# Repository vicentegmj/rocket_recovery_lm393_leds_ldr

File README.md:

# rocket_recovery_lm393_leds_uv

Sistema eletrônico cuja funcionalidade prevista é liberar um paraquedas logo após atingir o apogeu da trajetória do lançamento. O funcionamento do cirtuto é basedo no monitoramento de tensões elétricas em duas portas analógicas do CI LM393, as tensões são geradas por 2 LEDs UV. LED UV tem a paricularidade de criar uma tensão V nos seus terminais quando exposta á luz ultravioleta, no caso do foguete, a luz ultravioleta do Sol. Quando há inversão da tensão nos terminais o LM393 atravéz do seu pino de saída faz a saturação do TIP122 que passa a conduzir corrente elétrica direta da bateria de 9V fazendo a ignição da carga.

Esquema elétrico 26-06-2025

Circuito placa 11/07/2025

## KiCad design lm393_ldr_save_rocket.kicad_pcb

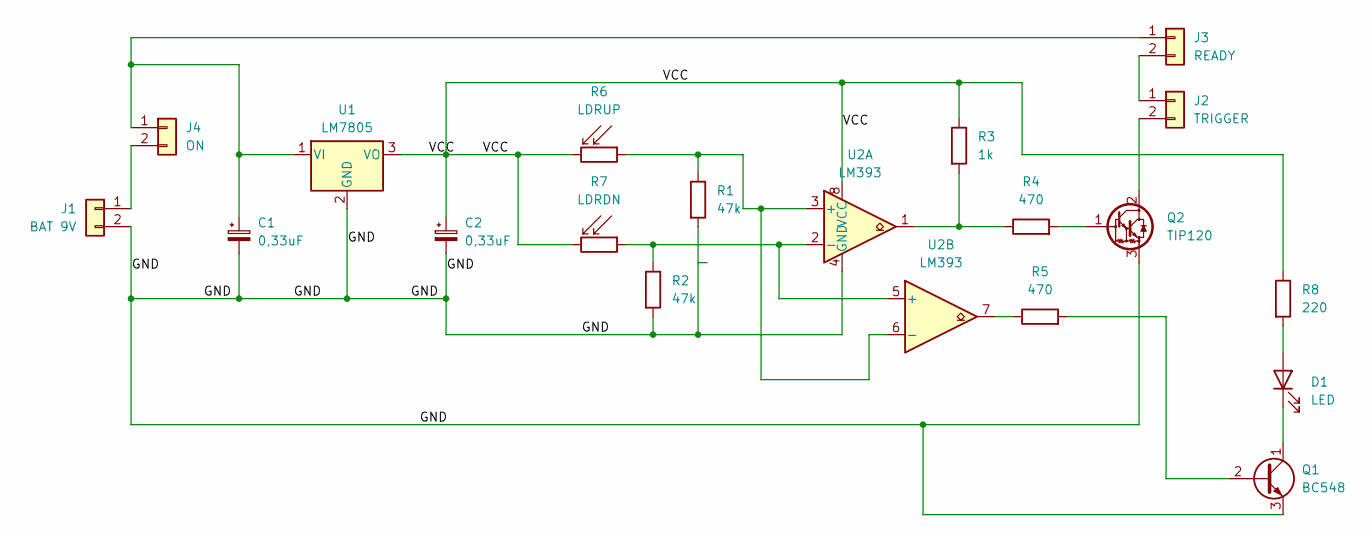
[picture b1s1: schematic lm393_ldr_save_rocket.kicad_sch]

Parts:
C1, C2: 0,33uF; CP_Radial_D4.0mm_P2.00mm
D1: LED; LED_D5.0mm
J1: BAT 9V; BarrelJack_GCT_DCJ200-10-A_Horizontal
J2: TRIGGER; TerminalBlock_Phoenix_MKDS-1,5-2-5.08_1x02_P5.08mm_Horizont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
J3: READY; SW_DIP_SPSTx01_Slide_6.7x4.1mm_W7.62mm_P2.54mm_LowProfile
J4: ON; SW_DIP_SPSTx01_Slide_6.7x4.1mm_W7.62mm_P2.54mm_LowProfile
Q1: BC548; TO-92L_Inline_Wide
Q2: TIP120; TO-220-3_Horizontal_TabDown
R1, R2: 47k; R_Axial_DIN0204_L3.6mm_D1.6mm_P5.08mm_Horizontal
R3: 1k; R_Axial_DIN0204_L3.6mm_D1.6mm_P5.08mm_Horizontal
R4, R5: 470; R_Axial_DIN0204_L3.6mm_D1.6mm_P5.08mm_Horizontal
R6: LDRUP; PinHeader_1x02_P2.54mm_Vertical
R7: LDRDN; PinHeader_1x02_P2.54mm_Vertical
R8: 220; R_Axial_DIN0204_L3.6mm_D1.6mm_P5.08mm_Horizontal
U1: LM7805; TO-220-3_Horizontal_TabDown
U2: LM393; DIP-8_296_ELL

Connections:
/GND: C1.2, C2.2, J1.2, Q1.3 (E), Q2.3 (E), R1.2, R2.2, U1.2 (GND), U2.4 (GND)
/VCC: C2.1, R3.1, R6.2, R7.2, R8.1, U1.3 (VO), U2.8 (VCC)
unnamed: D1.2 (A), R8.2
unnamed: D1.1 (K), Q1.1 (C)
unnamed: J1.1, J4.2
unnamed: J2.1, J3.2
unnamed: J2.2, Q2.2 (C)
unnamed: C1.1, J3.1, J4.1, U1.1 (VI)
unnamed: Q1.2 (B), R5.2
unnamed: Q2.1 (B), R4.2
unnamed: R3.2, R4.1, U2.1
unnamed: R5.1, U2.7
unnamed: R1.1, R6.1, U2.3 (+), U2.6 (-)
unnamed: R2.1, R7.1, U2.2 (-), U2.5 (+)

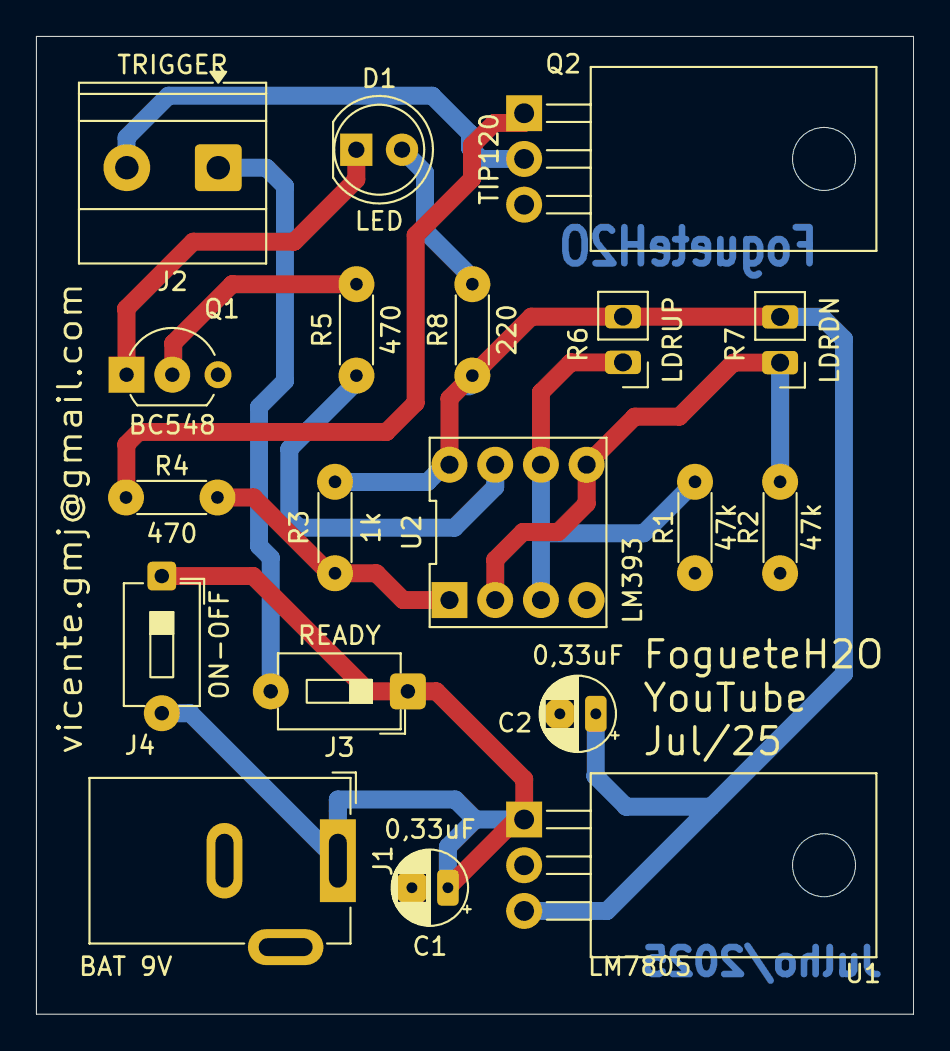
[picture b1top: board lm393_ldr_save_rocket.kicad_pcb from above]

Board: 2 copper layers, 48.7 x 54.3 mm, 19 parts (0 on the bottom side), 14 nets.

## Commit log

2025-06-26 Primeiro commit do projeto LM393 LDR Save Rocket
2025-06-26 ajustes de posicionamento de componentes na placa
2025-06-27 update de backup
2025-06-27 jumper de segurança
2025-06-27 basicamente update de backup
2025-06-29 novo tamanho 5x5 cm
2025-06-29 novo modelo placa
2025-07-02 posicionamento carga tip120
2025-07-10 finalizada com order para JCLPCB
